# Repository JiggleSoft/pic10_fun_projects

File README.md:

# JiggleSoft

Click [here](http://www.jigglesoft.co.uk) to visit the JiggleSoft web site

# Microchip PIC10 Fun Projects

Home on GitHub (https://github.com/JiggleSoft/pic10_fun_projects)

## Contact Details

Justin Lane (pic10funprojects@jigglesoft.co.uk)

## Why?

  * Why not?
  * It is fun to make cool stuff.
  * MCU is very cheap at approx. 50 pence each in small quantities.
  * Very limited resources (RAM,ROM,Stack,I/O):
    * Less to learn and remember.
      * Data Sheet is 88 pages for PIC10F200/202/204/206 ([Download](http://ww1.microchip.com/downloads/en/DeviceDoc/40001239F.pdf)).
    * Small ROM allows practical development in assembly language.
	  * Programs are limited in size so assembly language is practical.
	  * Get an appreciation of what is going on inside the CPU.
	* Learn to squeeze and make best use of every available resource.
	  * This is missing from the software these days where 3GHz multi-core CPUs with vast RAM and storage can be thrown at problems.
    * Simpler projects, so are quick to build.
  * Available in PDIP so no SMT soldering required.
  * Circuits can be wired on breadboards and made in classrooms.
  * PCB layouts are Stripboard friendly so no custom PCBs are necessary.

## Completed Projects

  * General 
    * Microchip PIC10 (and PIC12) Programming ZIF Socket Board.
      * Allows out-of-circuit programming of PIC10 and PIC12 MCU's via a PICKit 2,3,4, or any compatible programmer ([Buy](https://new.microchipdirect.com/product/search/all/pg164140)).

## Work-In-Progress

  * General 
    * Microchip PIC10 General Purpose Development Board.
      * General purpose board that can be built in various flavours to support wiring up projects on a bench with jumper leads.
  * Visible Light Emitting Diode (LED)
   * Flashing LED Test Program.
   * Morse Code Beacon.
   * Mood Light (RGB).
   * Matrix 8x8 with MAX7219 driver.
  * Joke
    * IR LED Annoying Covert Possessed Remote Control.

## For Consideration

  * Visible Light Emitting Diode (LED)
    * Die.
    * Decision Maker
    * Night Light (variation on Mood Light).
  * Jokes
    * IR LED Remote Control Jammer.
    * Annoying Sounds (PIC and Piezzo Sounder).
  * Games
    * Wild West Quick Draw Game
    * Reaction Game
    * Memory Game (Repeat Sequence)
    * Skill Electric Wire
    * LED 8x8 Game/Toy Hand Held
  * Cool
    * Morse Decoder
    * Video Demo
    * SoDAR
    * Organ
    * Fart Detector
  * To Classify
    * Line Follow
    * Environmentatl_Alarm_Humidity_Temp
    * Movement_Detector_Alarm

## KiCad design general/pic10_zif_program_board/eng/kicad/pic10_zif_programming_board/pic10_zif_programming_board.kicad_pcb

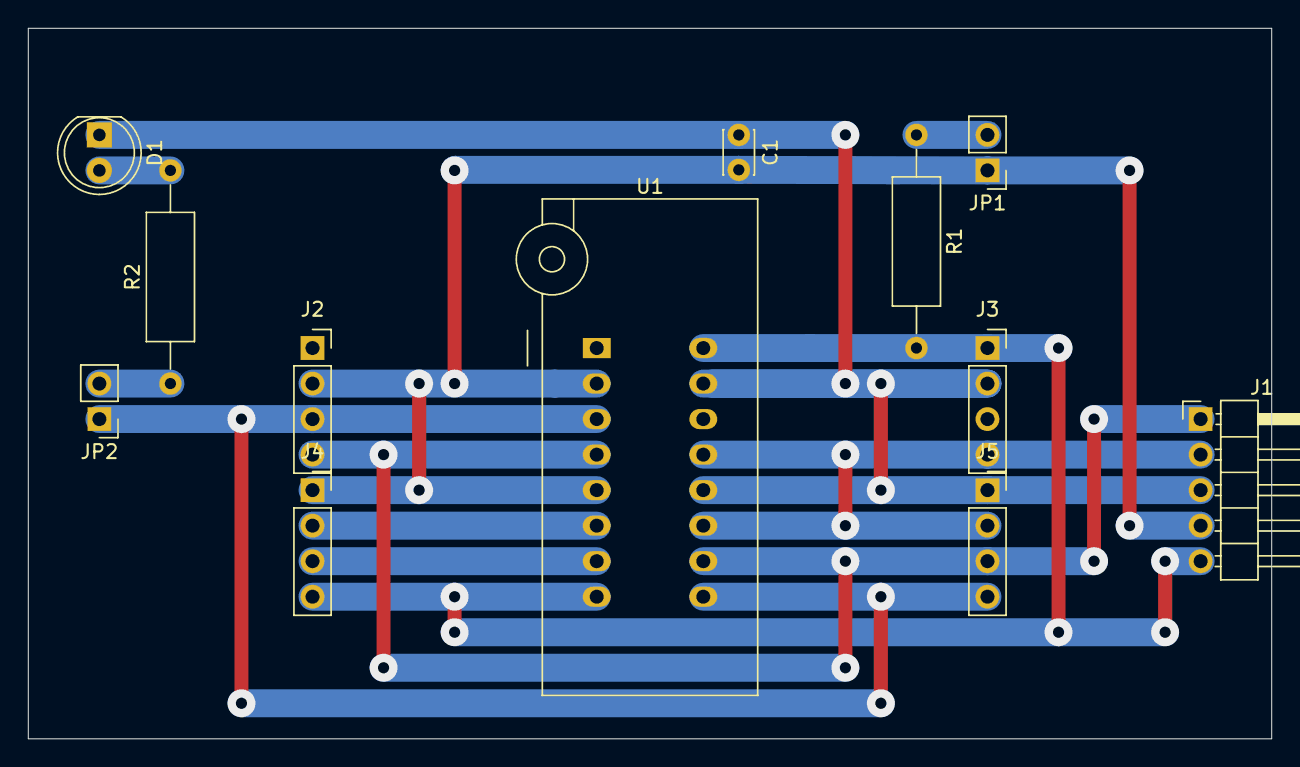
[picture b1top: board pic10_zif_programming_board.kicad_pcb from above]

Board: 2 copper layers, 88.9 x 50.8 mm, 12 parts (0 on the bottom side), 11 nets.

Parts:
C1: 0.1uF; C_Disc_D3.0mm_W2.0mm_P2.50mm
D1: LED; LED_D5.0mm
J1: Conn_01x05_Male; PinHeader_1x05_P2.54mm_Horizontal
J2, J3, J4, J5: Conn_01x04_Female; PinSocket_1x04_P2.54mm_Vertical
JP1, JP2: Jumper_NC_Small; PinHeader_1x02_P2.54mm_Vertical
R1: 10K; R_Axial_DIN0309_L9.0mm_D3.2mm_P15.24mm_Horizontal
R2: 330R; R_Axial_DIN0309_L9.0mm_D3.2mm_P15.24mm_Horizontal
U1: DIP .300 ZIF Socket; DIP_Socket-16_W4.3_W5.08_W7.62_W10.16_W10.9_3M_216-3340-00-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

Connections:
/GP2: J2.3, J5.4, JP2.1, U1.3, U1.9
/ICSPCLK: J1.1, J2.4, J5.3, U1.4, U1.10
/ICSPDAT: J1.2, J3.4, J5.2, U1.11, U1.13
/RA4: J4.3, U1.7
/RA5: J4.2, U1.6
/VDD: C1.2, J1.4, J2.2, J4.1, JP1.1, U1.2, U1.5
/VPP: J1.5, J3.1, J4.4, R1.2, U1.8, U1.16
/VSS: C1.1, D1.1, J1.3, J3.2, J5.1, U1.12, U1.15
unnamed: D1.2, R2.2
unnamed: JP1.2, R1.1
unnamed: JP2.2, R2.1

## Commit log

2019-04-19 Initial commit of LICENCE.txt, README.md, .gitignore file. Also the general PIC10 (and PIC12) out-of-circuit ZIF programming board. Build pictures and test application to follow shortly.

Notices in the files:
general/pic10_zif_program_board/eng/kicad/pic10_zif_programming_board/pic10_zif_programming_board.kicad_pcb:
Copyright (c) 2019 Justin Lane. All rights reserved.
